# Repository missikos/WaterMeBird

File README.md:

# WaterMeBird

##Video Instructions
https://www.youtube.com/playlist?list=PLXV-vJmVgkyYVAK37a0ae-BBcncbxYWD5

#Advanced:

##PCB:
TBA

##Programming:
TBA

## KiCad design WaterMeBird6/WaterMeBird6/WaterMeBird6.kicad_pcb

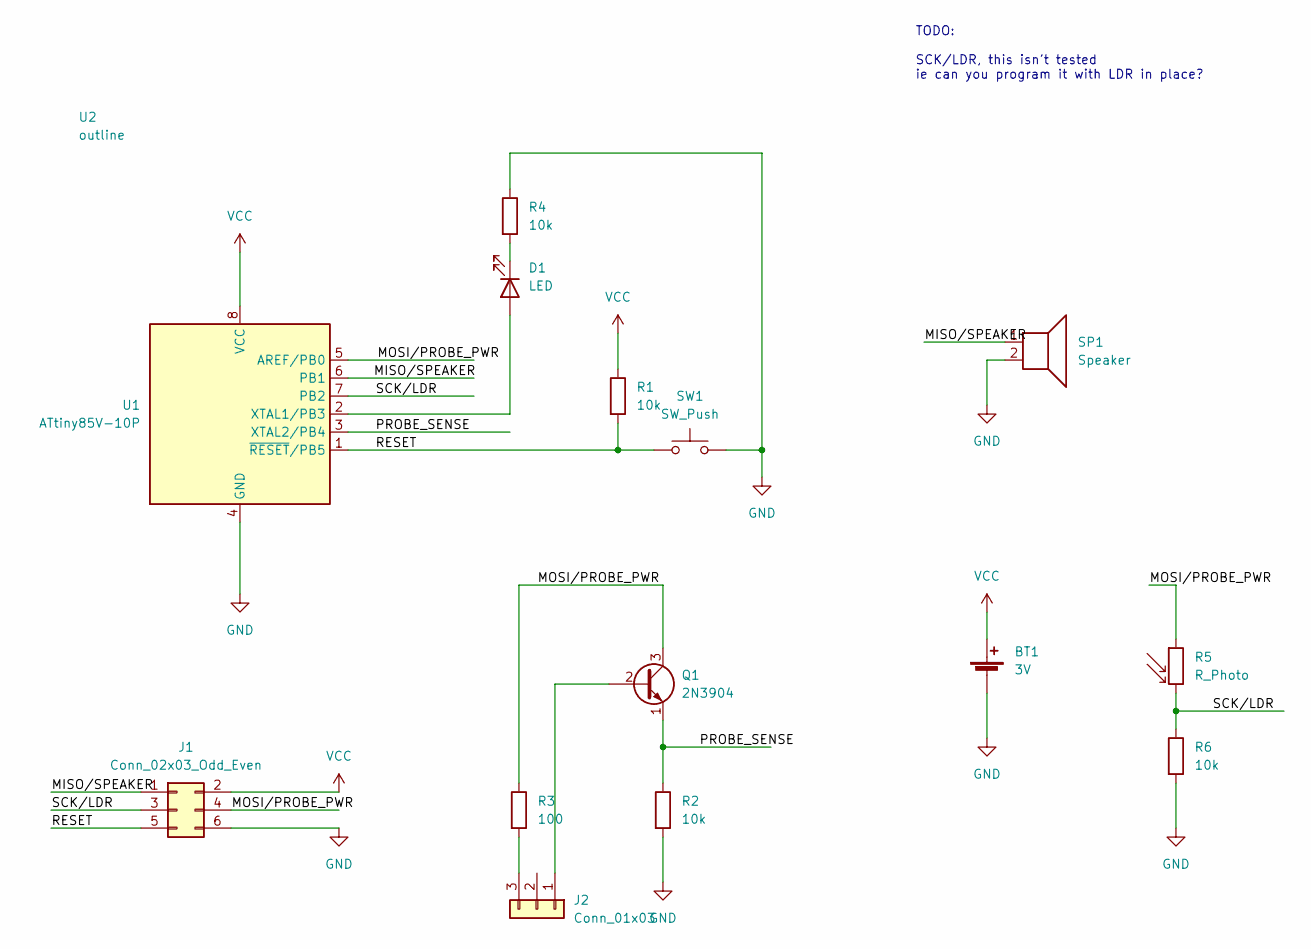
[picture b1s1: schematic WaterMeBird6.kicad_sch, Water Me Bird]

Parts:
BT1: 3V; BatteryHolder_Keystone_3002_1x2032
D1: LED; LED_D3.0mm_Thick
J1: Conn_02x03_Odd_Even; PinSocket_2x03_P2.54mm_Vertical
J2: Conn_01x03; TerminalBlock_1x03_P5.00mm_Thick
Q1: 2N3904; TO-92_Inline_Wide_Thick
R1, R2, R4, R6: 10k; R_Axial_DIN0309_L9.0mm_D3.2mm_P12.70mm_Horizontal_Thick
R3: 100; R_Axial_DIN0309_L9.0mm_D3.2mm_P12.70mm_Horizontal_Thick
R5: R_Photo; R_LDR_4.9x4.2mm_P2.54mm_Vertical_Thick
SP1: Speaker; MagneticBuzzer_Thick
SW1: SW_Push; SW_PUSH_6mm_H5mm_Thick
U1: ATtiny85V-10P; DIP-8_W7.62mm_Thick
U2: outline; bird_outline

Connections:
/MISO/SPEAKER: J1.1, SP1.1, U1.6 (PB1)
/MOSI/PROBE_PWR: J1.4, Q1.3 (C), R3.1, R5.1, U1.5 (AREF/PB0)
/PROBE_SENSE: Q1.1 (E), R2.1, U1.3 (XTAL2/PB4)
/RESET: J1.5, R1.2, SW1.1, U1.1 (~RESET/PB5)
/SCK/LDR: J1.3, R5.2, R6.1, U1.7 (PB2)
GND: BT1.2 (-), J1.6, R2.2, R4.1, R6.2, SP1.2, SW1.2, U1.4 (GND)
unnamed: D1.1 (K), R4.2
unnamed: D1.2 (A), U1.2 (XTAL1/PB3)
unnamed: J2.1, Q1.2 (B)
unnamed: J2.3, R3.2
VCC: BT1.1 (+), J1.2, R1.1, U1.8 (VCC)

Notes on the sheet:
TODO: SCK/LDR, this isn't tested ie can you program it with LDR in place?

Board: 2 copper layers, 15 parts (14 on the bottom side), 11 nets, no tracks yet.

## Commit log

2019-03-15 Initial and clean, this is V5.2
2021-06-04 docs
2022-03-29 Adding new version
2022-03-29 Added 'thick' version of footprints
2022-03-30 added outline and placed
